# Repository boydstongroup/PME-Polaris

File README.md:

#Polaris PME 3D Printer Conversion Guide

This repository contains the necessary files and instructions to convert a Creality Ender-3 FFF 3D printer into an open-source Powder Melt Extrusion (PME) 3D printer.

## Table of Contents

- [Introduction](#introduction)
- [Prerequisites](#prerequisites)
- [Conversion Process](#conversion-process)
- [Contribution](#contribution)

## Introduction

The Polaris PME 3D printer enables the use of custom materials without the need for expensive filamentation processes. It also facilitates recycling and compositing of bespoke polymers with specific physical or chemical properties. The conversion process involves 3D printing custom parts, soldering electrical components, and assembling the printer. This guide aims to help researchers and enthusiasts modify a Creality Ender-3 FFF 3D printer to build an affordable and reliable PME printing system.

## Prerequisites

- Access to a functioning FFF 3D printer (for printing custom parts)
- Necessary parts and tools as specified in the bill of materials
- Basic technical knowledge (soldering, assembling, etc.)

## Conversion Process

1. Clone the [PME-Polaris repository](https://github.com/boydstongroup/PME-Polaris.git) and explore the README file for detailed information about the bill of materials and 3D models.
2. Print the custom parts using the provided 3D models.
3. Gather all necessary components and tools.
4. Follow the step-by-step conversion guide to assemble your Polaris PME 3D printer.
5. Set up the firmware and software for the printer.
6. Test and calibrate the PME 3D printer according to the provided instructions.

## Contribution

The PME project is actively developed, and contributions from the open-source community are welcome. We encourage researchers and enthusiasts to modify, improve, and share their work to advance the field of 3D printing. If you have any questions, suggestions, or improvements, please submit an issue or pull request to the [PME-Polaris repository](https://github.com/boydstongroup/PME-Polaris.git).

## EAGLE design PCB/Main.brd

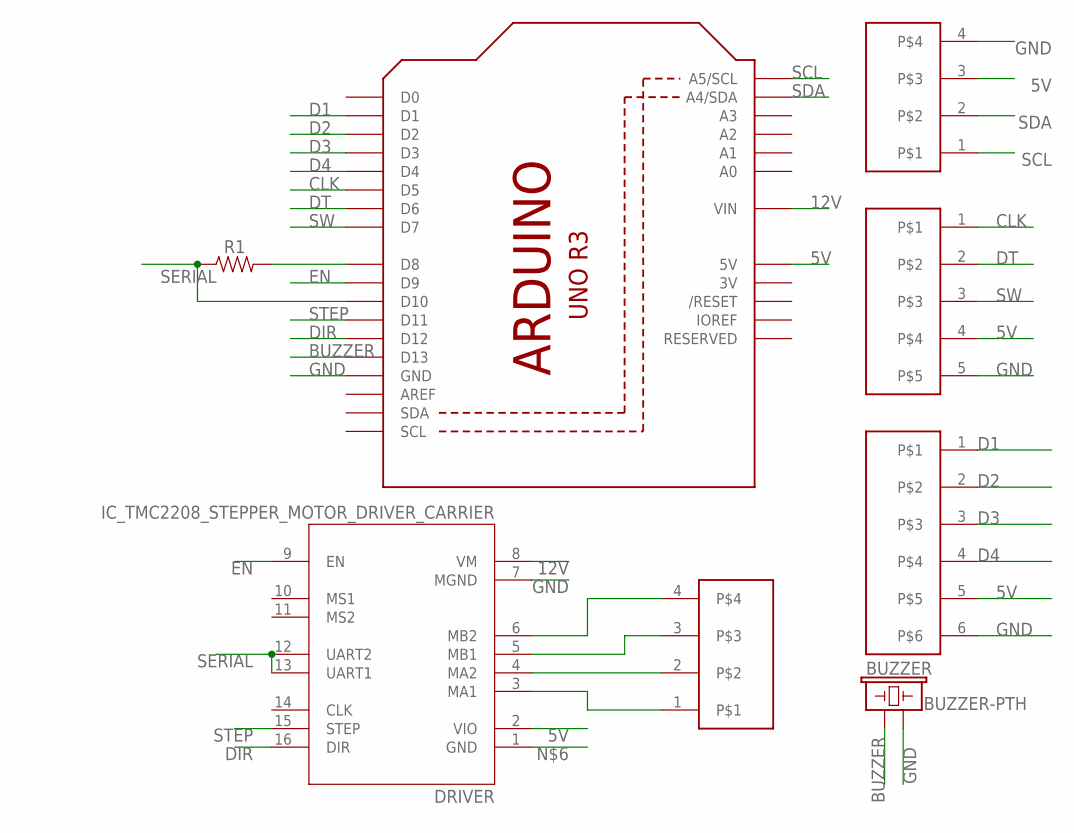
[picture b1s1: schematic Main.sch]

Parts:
BUZZER: BUZZER-PTH; BUZZER-12MM
DISPLAY: JST-XH-04-PIN-LONG-PAD; JST-XH-04-PACKAGE-LONG-PAD
DRIVER: IC_TMC2208_STEPPER_MOTOR_DRIVER_CARRIER
ENCODER: JST-XH-05-PIN-LONG-PAD; JST-XH-05-PACKAGE-LONG-PAD
MOTOR: JST-XH-04-PIN-LONG-PAD; JST-XH-04-PACKAGE-LONG-PAD
OUTPUT: JST-XH-06-PIN-LONG-PAD; JST-XH-06-PACKAGE-LONG-PAD
R1: AXIAL-0.3
U2: ARDUINOR3-BPLACE

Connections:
3V: U2.3V
5V: DISPLAY.3, DRIVER.2 (VIO), ENCODER.4, OUTPUT.5, U2.5V
12V: DRIVER.8 (VM), U2.VIN
BUZZER: BUZZER.+ (1), U2.D13
CLK: ENCODER.1, U2.D5
D1: OUTPUT.1, U2.D1
D2: OUTPUT.2, U2.D2
D3: OUTPUT.3, U2.D3
D4: OUTPUT.4, U2.D4
DIR: DRIVER.16 (DIR), U2.D12
DT: ENCODER.2, U2.D6
EN: DRIVER.9 (EN), U2.D9
GND: BUZZER.- (2), DISPLAY.4, DRIVER.7 (MGND), ENCODER.5, OUTPUT.6, U2.GND, U2.GND1 (GND), U2.GND2 (GND)
unnamed: DRIVER.3 (MA1), MOTOR.1
unnamed: DRIVER.4 (MA2), MOTOR.2
unnamed: DRIVER.5 (MB1), MOTOR.3
unnamed: DRIVER.6 (MB2), MOTOR.4
unnamed: R1.P$2 (2), U2.D8
SCL: DISPLAY.1, U2.A5 (A5/SCL)
SDA: DISPLAY.2, U2.A4 (A4/SDA)
SERIAL: DRIVER.12 (UART2), DRIVER.13 (UART1), R1.P$1 (1), U2.D10
STEP: DRIVER.15 (STEP), U2.D11
SW: ENCODER.3, U2.D7

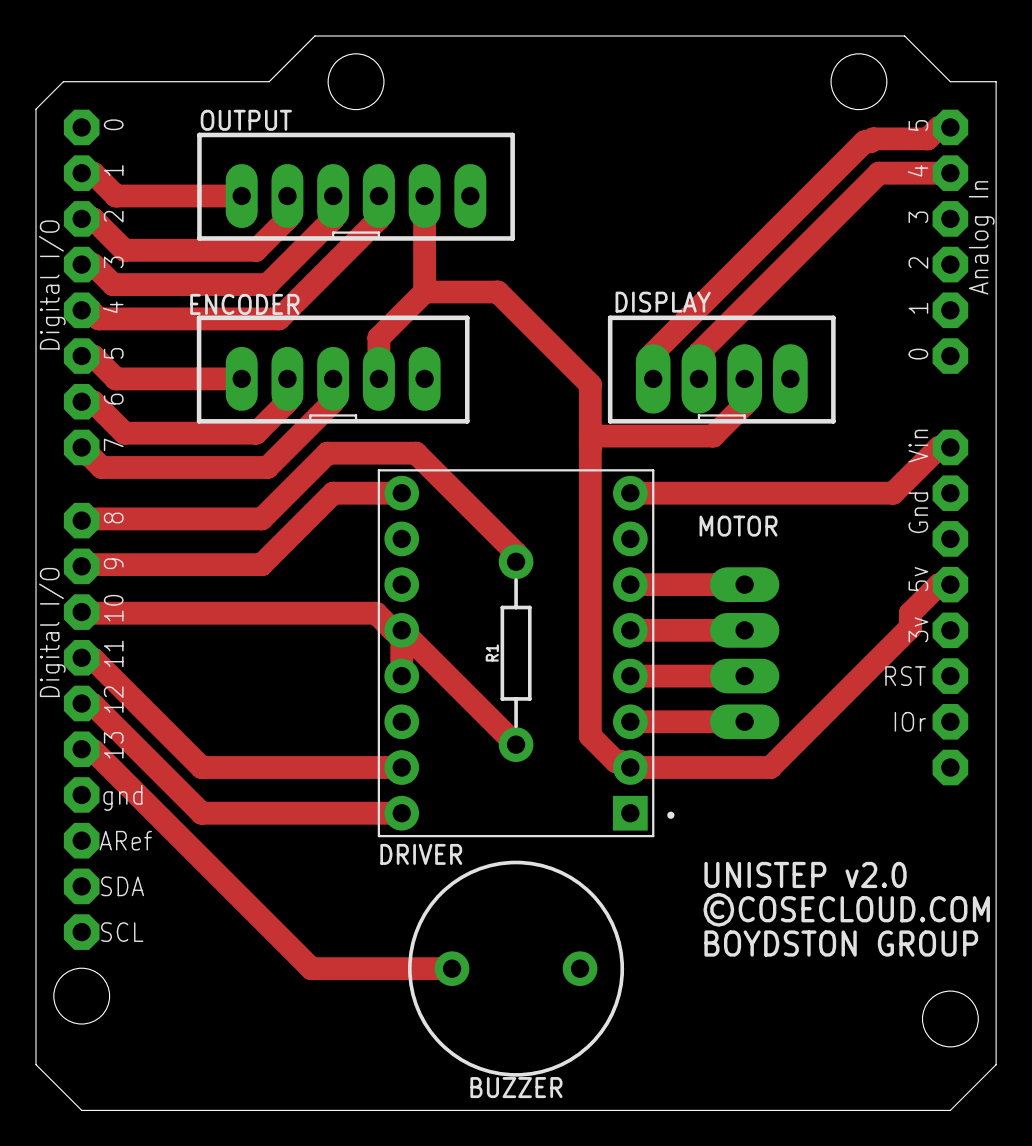
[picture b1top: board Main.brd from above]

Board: 2 copper layers, 53.3 x 59.7 mm, 8 parts (1 on the bottom side), 22 nets.

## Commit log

2022-06-28 Threaded STL updated
2023-04-11 readme update
2023-10-12 CAD Update

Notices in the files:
PCB/Main.brd:
©COSECLOUD.COM
